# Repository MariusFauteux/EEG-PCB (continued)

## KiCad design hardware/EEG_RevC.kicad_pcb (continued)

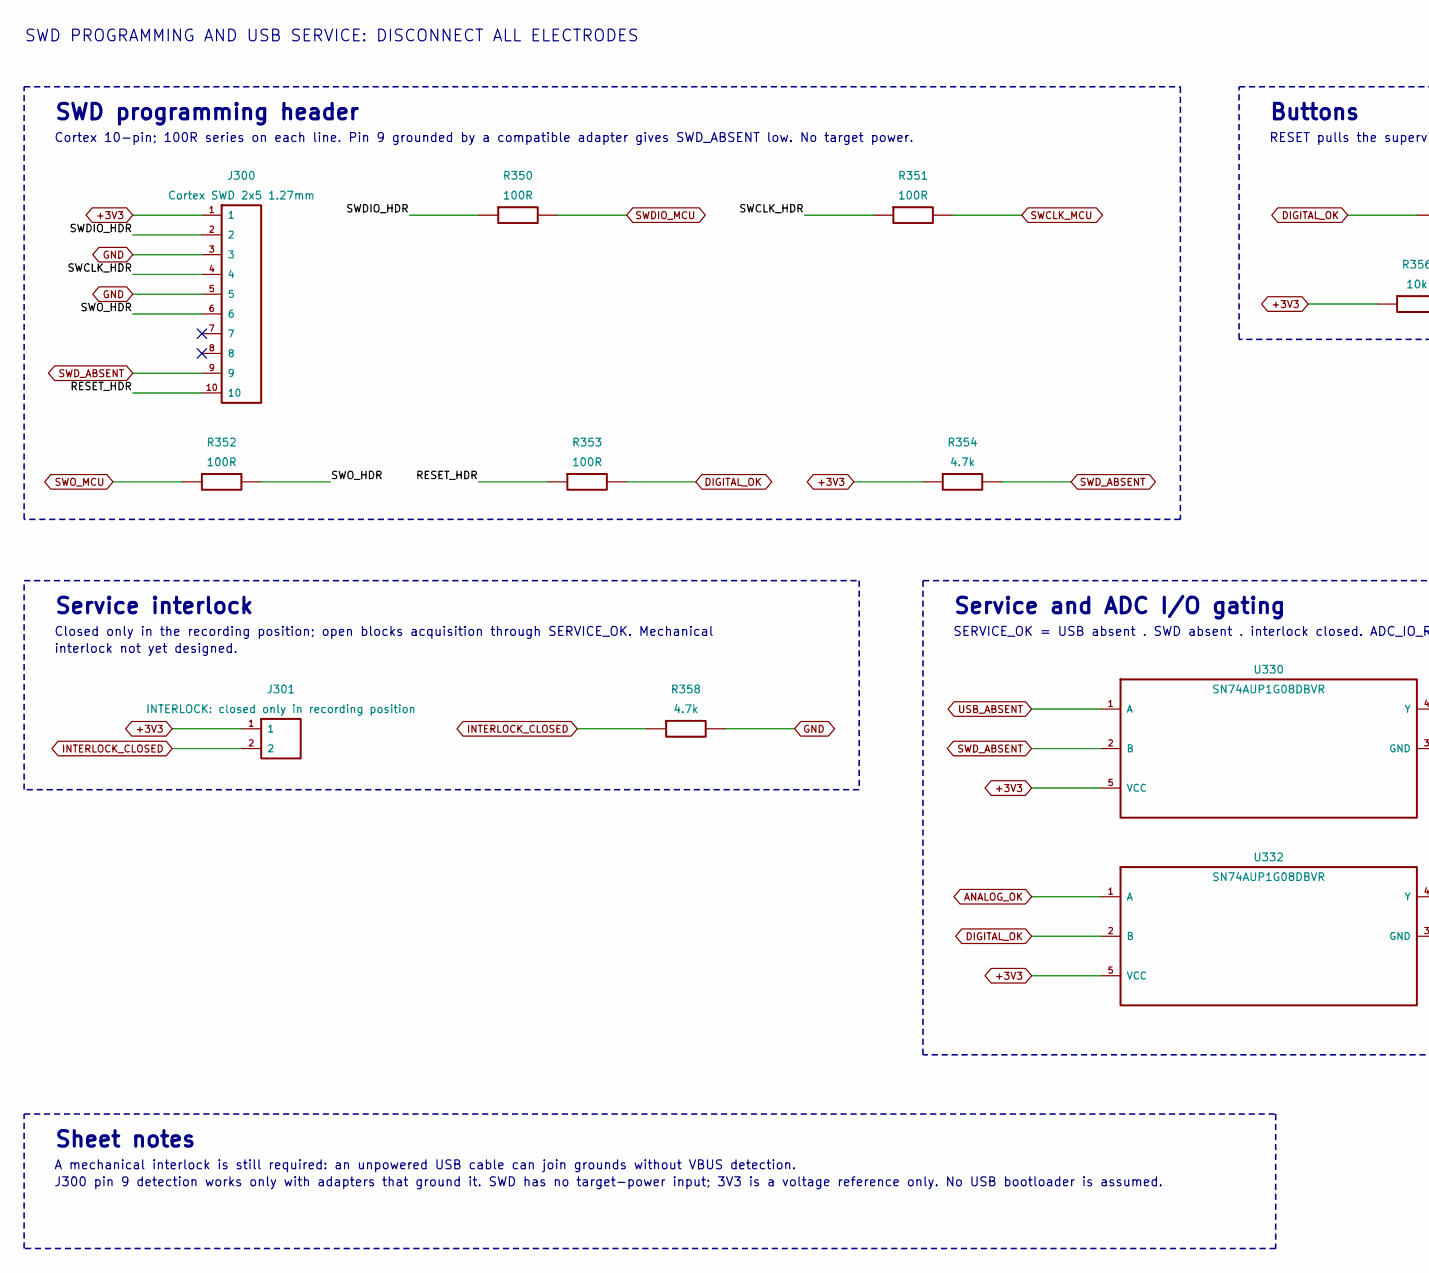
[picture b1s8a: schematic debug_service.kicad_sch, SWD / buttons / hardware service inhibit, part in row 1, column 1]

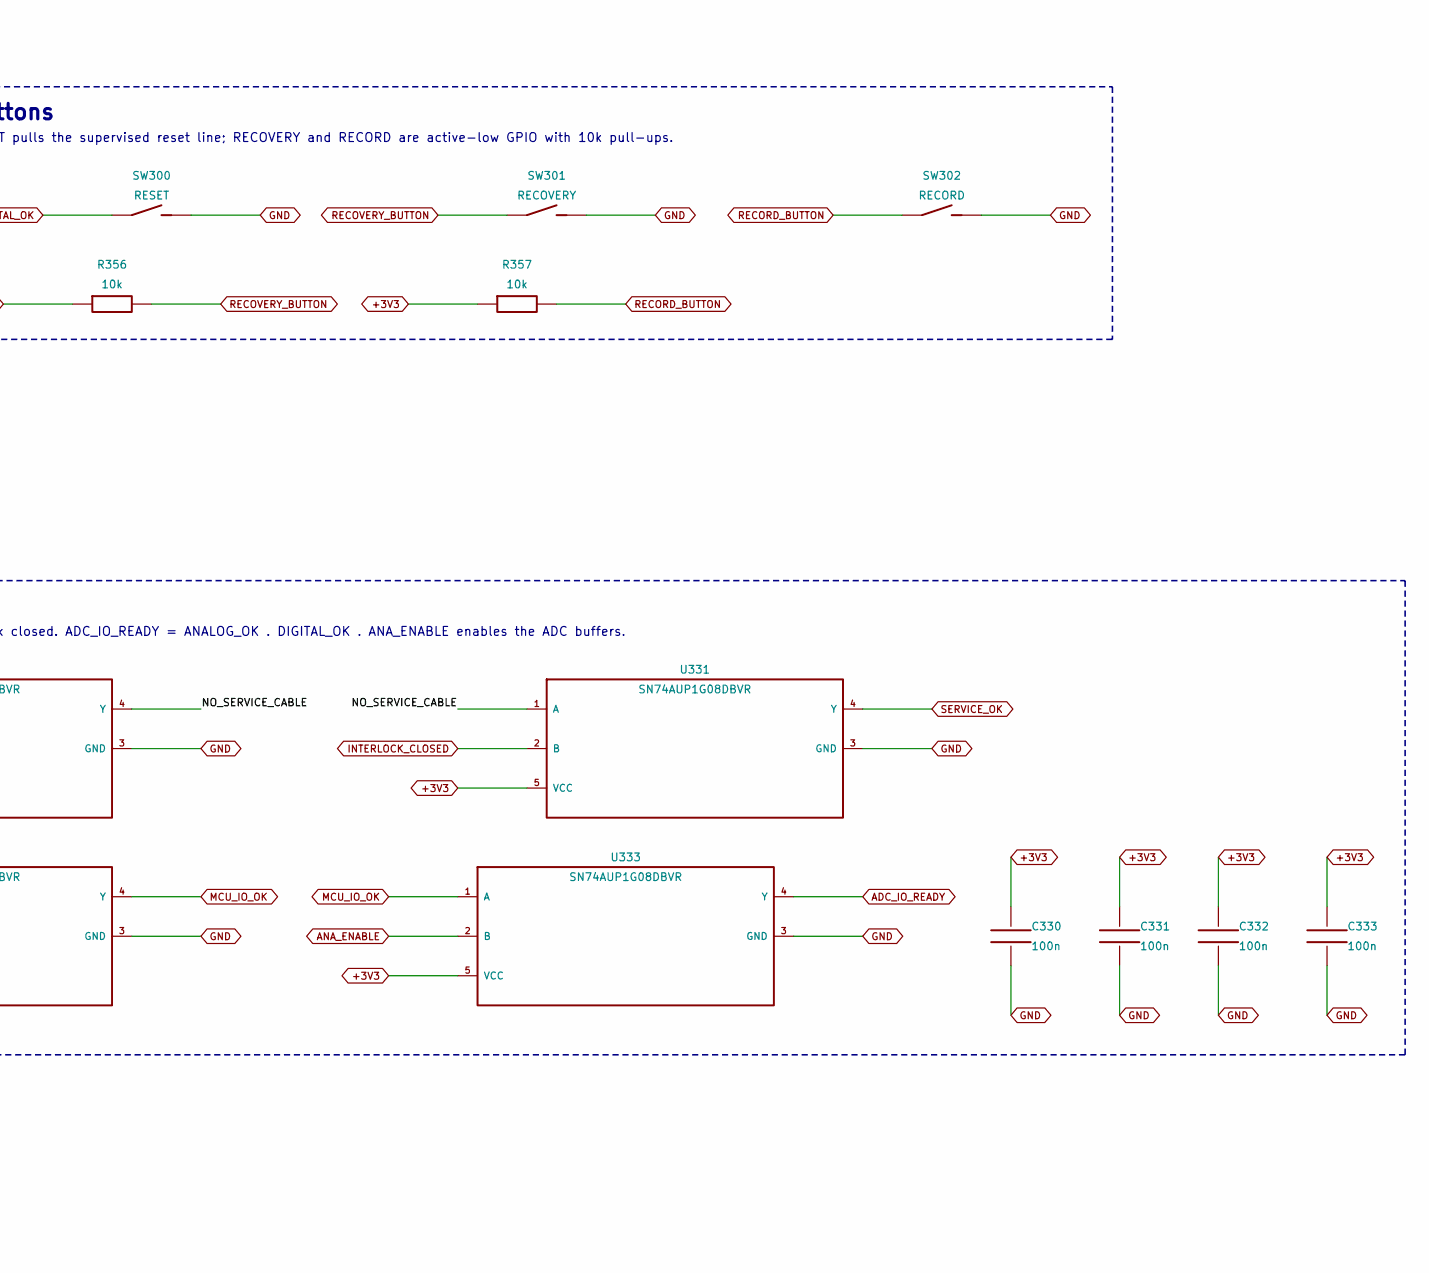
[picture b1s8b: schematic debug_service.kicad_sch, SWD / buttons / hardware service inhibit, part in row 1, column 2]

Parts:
C330, C331, C332, C333: 100n; C_0603_1608Metric; MPN GCM188R71H104KA57D
J300: Cortex SWD 2x5 1.27mm; PinHeader_2x05_P1.27mm_Vertical_SMD; MPN 3220-10-0300-00
J301: INTERLOCK: closed only in recording position; JST_PH_S2B-PH-K_1x02_P2.00mm_Horizontal; MPN S2B-PH-K-S
R350, R351, R352, R353: 100R; R_0603_1608Metric; MPN ERJ-3EKF1000V
R354, R358: 4.7k; R_0603_1608Metric; MPN ERJ-3EKF4701V
R356, R357: 10k; R_0603_1608Metric; MPN ERJ-3EKF1002V
SW300: RESET; SW_SPST_TL3342; MPN TL3342F160QG
SW301: RECOVERY; SW_SPST_TL3342; MPN TL3342F160QG
SW302: RECORD; SW_SPST_TL3342; MPN TL3342F160QG
U330, U331, U332, U333: SN74AUP1G08DBVR; SOT-23-5; MPN SN74AUP1G08DBVR

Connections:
+3V3: C330.1, C331.1, C332.1, C333.1, J300.1, J301.1, R354.1, R356.1, R357.1, U330.5 (VCC), U331.5 (VCC), U332.5 (VCC), U333.5 (VCC); also elsewhere on the board
/SWD / buttons / hardware service inhibit/NO_SERVICE_CABLE: U330.4 (Y), U331.1 (A)
/SWD / buttons / hardware service inhibit/RESET_HDR: J300.10, R353.1
/SWD / buttons / hardware service inhibit/SWCLK_HDR: J300.4, R351.1
/SWD / buttons / hardware service inhibit/SWDIO_HDR: J300.2, R350.1
/SWD / buttons / hardware service inhibit/SWO_HDR: J300.6, R352.2
ADC_IO_READY: U333.4 (Y); also elsewhere on the board
ANALOG_OK: U332.1 (A); also elsewhere on the board
ANA_ENABLE: U333.2 (B); also elsewhere on the board
DIGITAL_OK: R353.2, SW300.1, U332.2 (B); also elsewhere on the board
GND: C330.2, C331.2, C332.2, C333.2, J300.3, J300.5, R358.2, SW300.2, SW301.2, SW302.2, U330.3 (GND), U331.3 (GND), U332.3 (GND), U333.3 (GND); also elsewhere on the board
INTERLOCK_CLOSED: J301.2, R358.1, U331.2 (B); also elsewhere on the board
MCU_IO_OK: U332.4 (Y), U333.1 (A)
RECORD_BUTTON: R357.2, SW302.1; also elsewhere on the board
RECOVERY_BUTTON: R356.2, SW301.1; also elsewhere on the board
SERVICE_OK: U331.4 (Y); also elsewhere on the board
SWCLK_MCU: R351.2; also elsewhere on the board
SWDIO_MCU: R350.2; also elsewhere on the board
SWD_ABSENT: J300.9, R354.2, U330.2 (B)
SWO_MCU: R352.1; also elsewhere on the board
USB_ABSENT: U330.1 (A); also elsewhere on the board

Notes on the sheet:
SWD PROGRAMMING AND USB SERVICE: DISCONNECT ALL ELECTRODES
SWD programming header
Cortex 10-pin; 100R series on each line. Pin 9 grounded by a compatible adapter gives SWD_ABSENT low. No target power.
Buttons
RESET pulls the supervised reset line; RECOVERY and RECORD are active-low GPIO with 10k pull-ups.
Service interlock
Closed only in the recording position; open blocks acquisition through SERVICE_OK. Mechanical
interlock not yet designed.
Service and ADC I/O gating
SERVICE_OK = USB absent . SWD absent . interlock closed. ADC_IO_READY = ANALOG_OK . DIGITAL_OK . ANA_ENABLE enables the ADC buffers.
Sheet notes
A mechanical interlock is still required: an unpowered USB cable can join grounds without VBUS detection.
J300 pin 9 detection works only with adapters that ground it. SWD has no target-power input; 3V3 is a voltage reference only. No USB bootloader is assumed.

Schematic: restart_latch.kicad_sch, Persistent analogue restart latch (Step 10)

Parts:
C226, C227, C228: 100n; C_0603_1608Metric; MPN GCM188R71H104KA57D
TP230: RUN_ARMED; TestPoint_Pad_D1.0mm
U226, U228: SN74AUP1G08DBVR; SOT-23-5; MPN SN74AUP1G08DBVR
U227: SN74LVC1G74DCUR; VSSOP-8_2.3x2mm_P0.5mm; MPN SN74LVC1G74DCUR

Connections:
+3V3: C226.1, C227.1, C228.1, U226.5 (VCC), U227.2 (D), U227.7 (~PRE), U227.8 (VCC), U228.5 (VCC); also elsewhere on the board
GND: C226.2, C227.2, C228.2, U226.3 (GND), U227.4 (GND), U228.3 (GND); also elsewhere on the board
POWER_OK: U226.1 (A); also elsewhere on the board
RUN_ARMED: TP230.1, U227.5 (Q), U228.2 (B)
RUN_LATCHED: U228.4 (Y); also elsewhere on the board
RUN_PERMIT: U226.4 (Y), U227.6 (~CLR)
RUN_REQUEST: U227.1 (CLK), U228.1 (A); also elsewhere on the board
SERVICE_OK: U226.2 (B); also elsewhere on the board

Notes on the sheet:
PERSISTENT ANALOGUE RESTART LATCH (Step 10)
Run permit
RUN_PERMIT = POWER_OK . SERVICE_OK. Low on any SYS, pack or service fault.
Restart flip-flop
RUN_PERMIT low clears RUN_ARMED and holds it clear. A new RUN_REQUEST rising edge re-arms only while permitted. TP230 for
bench checks.
Latched run output
RUN_LATCHED = RUN_REQUEST . RUN_ARMED; replaces RUN_REQUEST in the analogue enable chain.
Sheet notes
ANA_ENABLE = SYS_OK . PACK_OK . SERVICE_OK . RUN_REQUEST . RUN_ARMED. Battery rebound cannot restart analogue power.
Power-up: supervisors hold POWER_OK low through their release delay, so U227 starts cleared.
Firmware: on any stop drive RUN_REQUEST low; to start, confirm SYS_OK and PACK_OK, hold RUN_REQUEST low >= 1 us, then high. Drive it directly from the GPIO (clock edge <= 10 ns/V, no RC).

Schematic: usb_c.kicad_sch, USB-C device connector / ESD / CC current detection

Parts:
C320, C322, C323: 100n; C_0603_1608Metric; MPN GCM188R71H104KA57D
C321: 1u 10V X7R; C_0805_2012Metric; MPN GCM21BR71E105KA56L
C324: 1u 50V X7R 0805 (VBUS_CON, at U323); C_0805_2012Metric; MPN GCM21BR71H105KA03L
C325: 1u 25V X7R 0805 (VBUS_POWER LDO); C_0805_2012Metric; MPN GCM21BR71E105KA56L
C326: 1u 25V X7R 0805 (LDO IN); C_0805_2012Metric; MPN GCM21BR71E105KA56L
C327: 1u 25V X7R 0805 (LDO OUT, module VBUS); C_0805_2012Metric; MPN GCM21BR71E105KA56L
D310, D311, D312: TPD2E2U06DCKR; SOT-323_SC-70; MPN TPD2E2U06DCKR
D324: BAT54 (U324 reverse-current bypass); SOT-23; MPN BAT54,215
J310: USB4105-GF-A; USB_C_Receptacle_GCT_USB4105-xx-A_16P_TopMnt_Horizontal; MPN USB4105-GF-A
R360: 887k 1%; R_0603_1608Metric; MPN ERJ-3EKF8873V
R361: 10k; R_0603_1608Metric; MPN ERJ-3EKF1002V
R362: 10k 1%; R_0603_1608Metric; MPN ERJ-3EKF1002V
R363: 100k 1%; R_0603_1608Metric; MPN ERJ-3EKF1003V
U320: TUSB320LAIRWBR; Texas_RWB0012A_X2QFN-12_1.6x1.6mm_P0.4mm; MPN TUSB320LAIRWBR
U321, U322: SN74LVC1G14DBVR; SOT-23-5; MPN SN74LVC1G14DBVR
U323: TPD1S514-1YZR (VBUS OVP 5.9-5.99 V); Texas_YZ0012_DSBGA-12_P0.4mm; MPN TPD1S514-1YZR
U324: TPS7A2050PDBVR (module VBUS 5.0 V); SOT-23-5; MPN TPS7A2050PDBVR

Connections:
+3V3: C320.1, C322.1, C323.1, R361.1, U320.12 (VDD), U321.5 (VCC), U322.5 (VCC); also elsewhere on the board
/USB-C device connector / ESD / CC current detection/USB_SENSE_LOGIC: R362.2, R363.1, U321.2 (A)
/USB-C device connector / ESD / CC current detection/VBUS_DETECT_R: R360.2, U320.4 (VBUS_DET)
CC1: D311.1 (IO1), J310.A5 (CC1), U320.1 (CC1)
CC2: D311.2 (IO2), J310.B5 (CC2), U320.2 (CC2)
GND: C320.2, C321.2, C322.2, C323.2, C324.2, C325.2, C326.2, C327.2, D310.3 (GND), D311.3 (GND), D312.3 (GND), J310.A1 (GND), J310.A12 (GND), J310.B1 (GND), J310.B12 (GND), J310.SH (SHIELD), R363.2, U320.3 (PORT), U320.5 (ADDR), U320.10 (GND), U320.11 (EN_N), U321.3 (GND), U322.3 (GND), U323.A1 (~EN), U323.A4 (GND), U323.B4 (GND), U323.C1 (GND), U323.C4 (GND), U324.2 (GND); also elsewhere on the board
MCU_VBUS: C327.1, D324.1 (A), U324.5 (OUT); also elsewhere on the board
POWER_SCL: U320.8 (SCL); also elsewhere on the board
POWER_SDA: U320.7 (SDA); also elsewhere on the board
USB_5V: C321.1, C326.1, D312.1 (IO1), D312.2 (IO2), D324.3 (K), U323.A2 (VBUS_SYS), U323.A3 (VBUS_SYS), U323.B2 (VBUS_SYS), U324.1 (IN), U324.3 (EN); also elsewhere on the board
USB_ABSENT: U321.4 (Y), U322.2 (A); also elsewhere on the board
USB_CC_INT_N: R361.2, U320.6 (INT_N); also elsewhere on the board
USB_DM: D310.2 (IO2), J310.A7 (D-), J310.B7 (D-); also elsewhere on the board
USB_DP: D310.1 (IO1), J310.A6 (D+), J310.B6 (D+); also elsewhere on the board
USB_PRESENT: U322.4 (Y); also elsewhere on the board
USB_VPWR: C325.1, R362.1, U323.B1 (VBUS_POWER)
VBUS_CON: C324.1, J310.A4 (VBUS), J310.A9 (VBUS), J310.B4 (VBUS), J310.B9 (VBUS), R360.1, U323.B3 (VBUS_CON), U323.C2 (VBUS_CON), U323.C3 (VBUS_CON)

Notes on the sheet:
USB-C 5 V SINK - NO PD, DATA TO MODULE, VBUS OVERVOLTAGE CUT-OFF, VBUS TO THE BQ25798 CHARGER
USB-C receptacle and ESD
USB 2.0 data to the module; duplicate contacts joined. TPD2E2U06 on D+/D-, CC and USB_5V is ESD only. J310 VBUS contacts are VBUS_CON, before the overvoltage switch.
VBUS overvoltage switch (Step 14)
TPD1S514-1: OVP 5.90-5.99 V, off in 100 ns, 30 V DC and 100 V surge on VBUS_CON, 39 mOhm. 20 ms delay + 3.5 ms soft start at plug-in, so the source sees
only C324 at attach. EN low: always enabled. VBUS_POWER (USB_VPWR, <= 5.5 V) feeds the USB-sense divider.
Module VBUS regulator (Step 14)
TPS7A2050: 5.0 V +/-1.5 % to module pad 31, because the nRF52840 VBUS pin is rated 5.5 V (5.8 V absolute) and the OVP ceiling is 5.99 V. D324 BAT54
carries reverse current to USB_5V after unplug (TI: <= 15 mA through the LDO).
CC sink controller
TUSB320LAI presents sink terminations and reports advertised current over I2C. No PD. VBUS_DET through 887k from the connector side (TI: system VBUS up to 28 V).
VBUS presence logic
Divider from USB_VPWR and Schmitt inverters give USB_ABSENT (gates SERVICE_OK) and USB_PRESENT (to MCU), also while U323 blocks an overvoltage source.
Sheet notes
Step 14: U323 TPD1S514-1 disconnects USB_5V from the connector above 5.99 V within 100 ns; VBUS_CON is rated 30 V DC. No duplicate Rd: the CC controller contains the sink terminations.
Route the USB 2.0 pair short and matched, directly to the module. Place U323 and C324 next to J310; keep VBUS_CON copper short and on the top layer (TI layout guide).

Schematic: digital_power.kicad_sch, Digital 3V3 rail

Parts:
C240: 10u 25V X7R 1206 (SYS); C_1206_3216Metric; MPN GRM31CR71E106KA12L
C241: 22u 25V X7R 1210; C_1210_3225Metric; MPN GRM32ER71E226KE15L
C242: 100n; C_0603_1608Metric; MPN GCM188R71H104KA57D
L240: 2.2uH XFL4020-222MEC; L_Coilcraft_XxL4020; MPN XFL4020-222MEC
R240: 100k; R_0603_1608Metric; MPN ERJ-3EKF1003V
R380, R382, R383: 100k reserved default; R_0603_1608Metric; MPN ERJ-3EKF1003V
U240: TPS62162DSGR; Texas_DSG0008A_WSON-8-1EP_2x2mm_P0.5mm_EP0.9x1.6mm; MPN TPS62162DSGR

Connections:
+3V3: C241.1, C242.1, L240.2, R240.1, U240.6 (VOS); also elsewhere on the board
/Digital 3V3 rail/BUCK_PG: R240.2, U240.8 (PG)
/Digital 3V3 rail/SW_DIG: L240.1, U240.7 (SW)
CHARGE_REQUEST: R380.1; also elsewhere on the board
GND: C240.2, C241.2, C242.2, R380.2, R382.2, R383.2, U240.1 (PGND), U240.4 (AGND), U240.5 (FB), U240.9 (EP); also elsewhere on the board
SD_POWER_EN: R383.1; also elsewhere on the board
STATUS_LED: R382.1; also elsewhere on the board
SYS: C240.1, U240.2 (VIN), U240.3 (EN); also elsewhere on the board

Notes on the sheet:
DIGITAL 3.3 V RAIL FROM SYS
3.3 V buck regulator
TPS62162 from SYS. Supplies module, logic, microSD and ADC DVDD. BUCK_PG is informational; DIGITAL_OK supervises.
Reserved control defaults
Pull-downs keep reserved MCU outputs (charge request, power hold, LED, SD power) defined until those circuits exist.
Sheet notes
TPS62162 runs whenever SYS is up: from the pack, or from USB through the charger. Soft-off is the BQ25798 ship mode (charger sheet), which removes SYS entirely.

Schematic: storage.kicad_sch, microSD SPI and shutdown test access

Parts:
C420: 22u 25V X7R 1210; C_1210_3225Metric; MPN GRM32ER71E226KE15L
C421: 100n 10V X7R; C_0603_1608Metric; MPN GCM188R71H104KA57D
C422: 10n; C_0603_1608Metric; MPN GCM1885C1H103JA16D
D420, D421, D422, D423: TPD2E2U06DCKR; SOT-323_SC-70; MPN TPD2E2U06DCKR
J420: DM3AT-SF-PEJM5; microSD_HC_Hirose_DM3AT-SF-PEJM5; MPN DM3AT-SF-PEJM5
R420, R421, R422, R423: 33R; R_0603_1608Metric; MPN ERJ-3EKF33R0V
R424, R425, R426, R427, R428, R430: 10k 1%; R_0603_1608Metric; MPN ERJ-3EKF1002V
R429: 100k; R_0603_1608Metric; MPN ERJ-3EKF1003V
R431: 100R; R_0603_1608Metric; MPN ERJ-3EKF1000V
TP420: +3V3; TestPoint_Pad_D1.0mm
TP421: GND; TestPoint_Pad_D1.0mm
TP422: BAT_WARN_OK; TestPoint_Pad_D1.0mm
TP423: SYS_OK; TestPoint_Pad_D1.0mm
TP424: PACK_OK; TestPoint_Pad_D1.0mm
TP425: DIGITAL_OK; TestPoint_Pad_D1.0mm

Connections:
+3V3: C420.1, C421.1, D423.2 (IO2), J420.4 (VDD), R424.1, R425.1, R426.1, R427.1, R428.1, R430.1, TP420.1; also elsewhere on the board
/microSD SPI and shutdown test access/CARD_CLK: D420.1 (IO1), J420.5 (CLK), R420.2
/microSD SPI and shutdown test access/CARD_CS_N: D421.1 (IO1), J420.2 (DAT3_CS_N), R422.2, R425.2
/microSD SPI and shutdown test access/CARD_DAT1: D422.1 (IO1), J420.8 (DAT1), R427.2
/microSD SPI and shutdown test access/CARD_DAT2: D422.2 (IO2), J420.1 (DAT2), R428.2
/microSD SPI and shutdown test access/CARD_DETECT_RAW_N: D423.1 (IO1), J420.9 (CD_B), R430.2, R431.1
/microSD SPI and shutdown test access/CARD_DI: D420.2 (IO2), J420.3 (CMD_DI), R421.2, R424.2
/microSD SPI and shutdown test access/CARD_DO: D421.2 (IO2), J420.7 (DAT0_DO), R423.2, R426.2
BAT_WARN_OK: TP422.1; also elsewhere on the board
DIGITAL_OK: TP425.1; also elsewhere on the board
GND: C420.2, C421.2, C422.2, D420.3 (GND), D421.3 (GND), D422.3 (GND), D423.3 (GND), J420.6 (VSS), J420.10 (CD_A), J420.SH (SHELL_x4), R429.2, TP421.1; also elsewhere on the board
PACK_OK: TP424.1; also elsewhere on the board
SD_CS_N: R422.1; also elsewhere on the board
SD_DETECT_N: C422.1, R431.2; also elsewhere on the board
SD_MISO: R423.1; also elsewhere on the board
SD_MOSI: R421.1; also elsewhere on the board
SD_SCLK: R420.1, R429.1; also elsewhere on the board
SYS_OK: TP423.1; also elsewhere on the board

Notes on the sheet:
microSD STORAGE (SPI, 3V3) - REMOVE CARD ONLY WITH BOARD POWER OFF
microSD socket and supply
DM3AT socket on the shared 3V3 rail; 22 uF bulk plus 100 nF. Remove the card only with power off.
SPI series resistors
33R damping between module and card; 100k keeps SCLK low at reset.
Card line pull-ups
10k on CMD/DAT lines as required by the SD SPI-mode start-up.
Card detect
Switch to GND, 10k pull-up and 100R/10 nF filter to SD_DETECT_N; software debounce.
Card-side ESD
TPD2E2U06 pairs at the socket on every card line and card detect.
Supply and status test points
Bench access to rails and supervisor outputs for shutdown testing.
Sheet notes
No load switch or hold-up reservoir; SD_POWER_EN is reserved. All card pull-ups use the shared 3V3 rail.
BAT_WARN_OK low: stop capture, drain queue, wait for card ready, sync best effort. No guaranteed flush interval.

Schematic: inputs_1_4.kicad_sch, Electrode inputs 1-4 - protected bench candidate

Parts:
C1, C2, C3, C4: 220p C0G 5% 50V; C_0603_1608Metric; MPN GCM1885C1H221JA16D
D501, D502, D503, D504: TPD2E2U06DCKR; SOT-323_SC-70; MPN TPD2E2U06DCKR
J1: CH1+
J2: CH1-
J3: CH2+
J4: CH2-
J5: CH3+
J6: CH3-
J7: CH4+
J8: CH4-
JP1, JP2, JP3, JP4: 1-2 bipolar / 2-3 REF; PinHeader_1x03_P2.54mm_Vertical; MPN 61300311121
R11, R12, R13, R14, R21, R22, R23, R24, R31, R32, R33, R34, R41, R42, R43, R44: 47k 0.1%; R_0805_2012Metric; MPN ERJ-PB6B4702V
R501, R502, R503, R504, R505, R506, R507, R508: 4.7k 0.1%; R_0805_2012Metric; MPN ERJ-PB6B4701V

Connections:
/Electrode inputs 1-4 - protected bench candidate/CLAMP1N: D501.2 (IO2), R14.2, R502.1
/Electrode inputs 1-4 - protected bench candidate/CLAMP1P: D501.1 (IO1), R12.2, R501.1
/Electrode inputs 1-4 - protected bench candidate/CLAMP2N: D502.2 (IO2), R24.2, R504.1
/Electrode inputs 1-4 - protected bench candidate/CLAMP2P: D502.1 (IO1), R22.2, R503.1
/Electrode inputs 1-4 - protected bench candidate/CLAMP3N: D503.2 (IO2), R34.2, R506.1
/Electrode inputs 1-4 - protected bench candidate/CLAMP3P: D503.1 (IO1), R32.2, R505.1
/Electrode inputs 1-4 - protected bench candidate/CLAMP4N: D504.2 (IO2), R44.2, R508.1
/Electrode inputs 1-4 - protected bench candidate/CLAMP4P: D504.1 (IO1), R42.2, R507.1
/Electrode inputs 1-4 - protected bench candidate/NSEL1: JP1.2, R13.1
/Electrode inputs 1-4 - protected bench candidate/NSEL2: JP2.2, R23.1
/Electrode inputs 1-4 - protected bench candidate/NSEL3: JP3.2, R33.1
/Electrode inputs 1-4 - protected bench candidate/NSEL4: JP4.2, R43.1
ADC_IN1N: C1.2, R502.2; also elsewhere on the board
ADC_IN1P: C1.1, R501.2; also elsewhere on the board
ADC_IN2N: C2.2, R504.2; also elsewhere on the board
ADC_IN2P: C2.1, R503.2; also elsewhere on the board
ADC_IN3N: C3.2, R506.2; also elsewhere on the board
ADC_IN3P: C3.1, R505.2; also elsewhere on the board
ADC_IN4N: C4.2, R508.2; also elsewhere on the board
ADC_IN4P: C4.1, R507.2; also elsewhere on the board
E1N: J2.1, JP1.1; also elsewhere on the board
E1P: J1.1, R11.1; also elsewhere on the board
E2N: J4.1, JP2.1; also elsewhere on the board
E2P: J3.1, R21.1; also elsewhere on the board
E3N: J6.1, JP3.1; also elsewhere on the board
E3P: J5.1, R31.1; also elsewhere on the board
E4N: J8.1, JP4.1; also elsewhere on the board
E4P: J7.1, R41.1; also elsewhere on the board
GND: D501.3 (GND), D502.3 (GND), D503.3 (GND), D504.3 (GND); also elsewhere on the board
unnamed: R11.2, R12.1
unnamed: R13.2, R14.1
unnamed: R21.2, R22.1
unnamed: R23.2, R24.1
unnamed: R31.2, R32.1
unnamed: R33.2, R34.1
unnamed: R41.2, R42.1
unnamed: R43.2, R44.1
REF_BUF: JP1.3, JP2.3, JP3.3, JP4.3; also elsewhere on the board

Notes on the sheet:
ELECTRODE INPUTS CH1-CH4 - 94k BEFORE CLAMP, 4.7k AFTER CLAMP. NO HUMAN CONNECTION
Channel 1 input network
CH1+ and CH1- each pass 2 x 47k, the TVS clamp, then 4.7k into the ADC; 220 pF C0G across the pair. JP1 selects bipolar (1-2) or the buffered shared REF, REF_BUF (2-3), for the negative leg.
Channel 2 input network
CH2+ and CH2- each pass 2 x 47k, the TVS clamp, then 4.7k into the ADC; 220 pF C0G across the pair. JP2 selects bipolar (1-2) or the buffered shared REF, REF_BUF (2-3), for the negative leg.
Channel 3 input network
CH3+ and CH3- each pass 2 x 47k, the TVS clamp, then 4.7k into the ADC; 220 pF C0G across the pair. JP3 selects bipolar (1-2) or the buffered shared REF, REF_BUF (2-3), for the negative leg.
Channel 4 input network
CH4+ and CH4- each pass 2 x 47k, the TVS clamp, then 4.7k into the ADC; 220 pF C0G across the pair. JP4 selects bipolar (1-2) or the buffered shared REF, REF_BUF (2-3), for the negative leg.
Sheet notes
TPD2E2U06 leakage limit applies at 2.5 V. The ground clamp is not isolation. Fit one shunt per JP; change it with power off.
JP pin 3 is REF_BUF, the buffered REF electrode; it passes through the same negative-leg network as a bipolar electrode. No extra capacitors from inputs to GND.

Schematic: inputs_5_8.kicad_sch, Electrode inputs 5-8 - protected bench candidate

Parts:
C5, C6, C7, C8: 220p C0G 5% 50V; C_0603_1608Metric; MPN GCM1885C1H221JA16D
D505, D506, D507, D508: TPD2E2U06DCKR; SOT-323_SC-70; MPN TPD2E2U06DCKR
J9: CH5+
J10: CH5-
J11: CH6+
J12: CH6-
J13: CH7+
J14: CH7-
J15: CH8+
J16: CH8-
JP5, JP6, JP7, JP8: 1-2 bipolar / 2-3 REF; PinHeader_1x03_P2.54mm_Vertical; MPN 61300311121
R51, R52, R53, R54, R61, R62, R63, R64, R71, R72, R73, R74, R81, R82, R83, R84: 47k 0.1%; R_0805_2012Metric; MPN ERJ-PB6B4702V
R509, R510, R511, R512, R513, R514, R515, R516: 4.7k 0.1%; R_0805_2012Metric; MPN ERJ-PB6B4701V

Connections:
/Electrode inputs 5-8 - protected bench candidate/CLAMP5N: D505.2 (IO2), R54.2, R510.1
/Electrode inputs 5-8 - protected bench candidate/CLAMP5P: D505.1 (IO1), R52.2, R509.1
/Electrode inputs 5-8 - protected bench candidate/CLAMP6N: D506.2 (IO2), R64.2, R512.1
/Electrode inputs 5-8 - protected bench candidate/CLAMP6P: D506.1 (IO1), R62.2, R511.1
/Electrode inputs 5-8 - protected bench candidate/CLAMP7N: D507.2 (IO2), R74.2, R514.1
/Electrode inputs 5-8 - protected bench candidate/CLAMP7P: D507.1 (IO1), R72.2, R513.1
/Electrode inputs 5-8 - protected bench candidate/CLAMP8N: D508.2 (IO2), R84.2, R516.1
/Electrode inputs 5-8 - protected bench candidate/CLAMP8P: D508.1 (IO1), R82.2, R515.1
/Electrode inputs 5-8 - protected bench candidate/NSEL5: JP5.2, R53.1
/Electrode inputs 5-8 - protected bench candidate/NSEL6: JP6.2, R63.1
/Electrode inputs 5-8 - protected bench candidate/NSEL7: JP7.2, R73.1
/Electrode inputs 5-8 - protected bench candidate/NSEL8: JP8.2, R83.1
ADC_IN5N: C5.2, R510.2; also elsewhere on the board
ADC_IN5P: C5.1, R509.2; also elsewhere on the board
ADC_IN6N: C6.2, R512.2; also elsewhere on the board
ADC_IN6P: C6.1, R511.2; also elsewhere on the board
ADC_IN7N: C7.2, R514.2; also elsewhere on the board
ADC_IN7P: C7.1, R513.2; also elsewhere on the board
ADC_IN8N: C8.2, R516.2; also elsewhere on the board
ADC_IN8P: C8.1, R515.2; also elsewhere on the board
E5N: J10.1, JP5.1; also elsewhere on the board
E5P: J9.1, R51.1; also elsewhere on the board
E6N: J12.1, JP6.1; also elsewhere on the board
E6P: J11.1, R61.1; also elsewhere on the board
E7N: J14.1, JP7.1; also elsewhere on the board
E7P: J13.1, R71.1; also elsewhere on the board
E8N: J16.1, JP8.1; also elsewhere on the board
E8P: J15.1, R81.1; also elsewhere on the board
GND: D505.3 (GND), D506.3 (GND), D507.3 (GND), D508.3 (GND); also elsewhere on the board
unnamed: R51.2, R52.1
unnamed: R53.2, R54.1
unnamed: R61.2, R62.1
unnamed: R63.2, R64.1
unnamed: R71.2, R72.1
unnamed: R73.2, R74.1
unnamed: R81.2, R82.1
unnamed: R83.2, R84.1
REF_BUF: JP5.3, JP6.3, JP7.3, JP8.3; also elsewhere on the board

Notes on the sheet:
ELECTRODE INPUTS CH5-CH8 - 94k BEFORE CLAMP, 4.7k AFTER CLAMP. NO HUMAN CONNECTION
Channel 5 input network
CH5+ and CH5- each pass 2 x 47k, the TVS clamp, then 4.7k into the ADC; 220 pF C0G across the pair. JP5 selects bipolar (1-2) or the buffered shared REF, REF_BUF (2-3), for the negative leg.
Channel 6 input network
CH6+ and CH6- each pass 2 x 47k, the TVS clamp, then 4.7k into the ADC; 220 pF C0G across the pair. JP6 selects bipolar (1-2) or the buffered shared REF, REF_BUF (2-3), for the negative leg.
Channel 7 input network
CH7+ and CH7- each pass 2 x 47k, the TVS clamp, then 4.7k into the ADC; 220 pF C0G across the pair. JP7 selects bipolar (1-2) or the buffered shared REF, REF_BUF (2-3), for the negative leg.
Channel 8 input network
CH8+ and CH8- each pass 2 x 47k, the TVS clamp, then 4.7k into the ADC; 220 pF C0G across the pair. JP8 selects bipolar (1-2) or the buffered shared REF, REF_BUF (2-3), for the negative leg.
Sheet notes
TPD2E2U06 leakage limit applies at 2.5 V. The ground clamp is not isolation. Fit one shunt per JP; change it with power off.
JP pin 3 is REF_BUF, the buffered REF electrode; it passes through the same negative-leg network as a bipolar electrode. No extra capacitors from inputs to GND.

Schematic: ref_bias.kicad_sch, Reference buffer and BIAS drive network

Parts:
C500: 100n 16V X7R (at U500 V+); C_0603_1608Metric; MPN GCM188R71H104KA57D
C501: 1u 10V X7R; C_0805_2012Metric; MPN GCM21BR71E105KA56L
CFB1: 10n C0G 5% 50V; C_0603_1608Metric; MPN GCM1885C1H103JA16D
D509, D510: TPD2E2U06DCKR; SOT-323_SC-70; MPN TPD2E2U06DCKR
J500: ELECTRODE HARNESS 2x10 (keyed box header); IDC-Header_2x10_P2.54mm_Vertical; MPN 61202021621
JBIAS1: BIAS electrode
JP9: REF test: REF electrode -> CH8- (JP8 1-2); PinHeader_1x02_P2.54mm_Vertical; MPN 61300211121
JP10: BIAS test: BIAS electrode -> CH7- (JP7 1-2); PinHeader_1x02_P2.54mm_Vertical; MPN 61300211121
JREF1: REF electrode
R517, R518: 47k 0.1%; R_0805_2012Metric; MPN ERJ-PB6B4702V
R519: 4.7k 0.1%; R_0805_2012Metric; MPN ERJ-PB6B4701V
RB1, RB2: 499k 0.1%; R_0805_2012Metric; MPN ERJ-PB6B4993V
RFB1: 1M; R_0805_2012Metric; MPN ERJ-PB6B1004V
RZB1: 100k 0.1%; R_0805_2012Metric; MPN ERJ-PB6B1003V
U500: OPA376AIDBVR; SOT-23-5; MPN OPA376AIDBVR

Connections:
+5VA: C500.1, C501.1, U500.5 (V+); also elsewhere on the board
/Reference buffer and BIAS drive network/BIAS_COMP: CFB1.2, RZB1.1
/Reference buffer and BIAS drive network/BIAS_MID: D509.1 (IO1), D509.2 (IO2), RB1.2, RB2.1
/Reference buffer and BIAS drive network/REF_BUF_IN: R519.2, U500.3 (+IN)
/Reference buffer and BIAS drive network/REF_CLAMP: D510.1 (IO1), D510.2 (IO2), R518.2, R519.1
/Reference buffer and BIAS drive network/REF_MID: R517.2, R518.1
ADC_BIASINV: RFB1.2, RZB1.2; also elsewhere on the board
ADC_BIASOUT: CFB1.1, RB1.1, RFB1.1; also elsewhere on the board
BIAS_ELEC: J500.18, JBIAS1.1, JP10.1, RB2.2
E1N: J500.2; also elsewhere on the board
E1P: J500.1; also elsewhere on the board
E2N: J500.4; also elsewhere on the board
E2P: J500.3; also elsewhere on the board
E3N: J500.6; also elsewhere on the board
E3P: J500.5; also elsewhere on the board
E4N: J500.8; also elsewhere on the board
E4P: J500.7; also elsewhere on the board
E5N: J500.10; also elsewhere on the board
E5P: J500.9; also elsewhere on the board
E6N: J500.12; also elsewhere on the board
E6P: J500.11; also elsewhere on the board
E7N: J500.14, JP10.2; also elsewhere on the board
E7P: J500.13; also elsewhere on the board
E8N: J500.16, JP9.2; also elsewhere on the board
E8P: J500.15; also elsewhere on the board
GND: C500.2, C501.2, D509.3 (GND), D510.3 (GND), U500.2 (V-); also elsewhere on the board
REF_BUF: U500.1 (OUT), U500.4 (-IN); also elsewhere on the board
REF_RAW: J500.17, JP9.1, JREF1.1, R517.1

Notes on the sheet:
REFERENCE BUFFER AND BIAS ELECTRODES - STEP 12 BUFFERED REF, STEP 8 BIAS LOOP, BENCH ONLY
REF electrode and buffer (Step 12)
REF electrode -> 2 x 47k -> D510 clamp -> 4.7k -> OPA376 unity follower. REF_BUF feeds JP1-JP8 pin 3; each selected channel keeps its own 94k / clamp / 4.7k. U500 on +5VA, so it is off and clamped with the
ADC.
BIAS output network
RB1 + RB2 (2 x 499k) limit body current; D509 clamps the midpoint to GND.
Electrode harness J500 (Step 13)
J500 2x10 keyed box header: pins 1-16 CH1+ to CH8- (odd +, even -), 17 REF, 18 BIAS, 19-20 unused. The electrode symbols
J1-J16, JREF1 and JBIAS1 are the off-board leads.
Electrode impedance test links (Rev C12)
Normally open. JP9 puts the REF electrode on CH8- (set JP8 1-2, no CH8- electrode); JP10 puts the BIAS electrode on CH7- (set
JP7 1-2, no CH7- electrode). The ADS1299 lead-off source then measures it through the channel's own 94k network.
BIAS loop compensation
Lead-lag feedback 1M || (100k + 10 nF C0G) between BIASOUT and BIASINV for >= 47 deg modelled phase margin.
Sheet notes
REF is an electrode, not the ADC reference and not GND. It now drives only the U500 follower: channels on REF share no electrode impedance, and the REF electrode carries one leg of leakage instead of up
to eight.
Firmware: set BIASREF_INT = 1 in the same CONFIG3 write that sets PD_BIAS = 1; monitor BIAS_STAT.
Do not inject sustained overvoltage or connect a person. RB1/RB2 need pulse- and voltage-rated parts. +5VA backfeed is clamped by Q201 (analog sheet).

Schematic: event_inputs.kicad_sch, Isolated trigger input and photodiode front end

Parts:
C600: 100n 10V X7R (within 1 cm of U600 pins 4/6); C_0603_1608Metric; MPN GCM188R71H104KA57D
C610: 15p C0G 5% 50V 0402; C_0402_1005Metric; MPN GCM1555C1H150JA16D
C611, C614: 100n; C_0603_1608Metric; MPN GCM188R71H104KA57D
C612, C613, C615: 100n 10V X7R; C_0603_1608Metric; MPN GCM188R71H104KA57D
D600: 1N4148WS (LED reverse clamp); D_SOD-323; MPN 1N4148WS-7-F
D601: TPD2E2U06DCKR; SOT-323_SC-70; MPN TPD2E2U06DCKR
J600: TRIGGER IN (BNC, shell = isolated return); BNC_Amphenol_031-6575_Horizontal; MPN 031-6575
J601: PHOTODIODE (K, A; part TBD); JST_PH_S2B-PH-K_1x02_P2.00mm_Horizontal; MPN S2B-PH-K-S
R600: 620R 1% 0.25W; R_1206_3216Metric; MPN ERJ-8ENF6200V
R601, R616: 100R; R_0603_1608Metric; MPN ERJ-3EKF1000V
R610, R617: 1k; R_0603_1608Metric; MPN ERJ-3EKF1001V
R611: 33k 0.1%; R_0603_1608Metric; MPN ERA-3ARB333V
R612: 64.9k 1%; R_0603_1608Metric; MPN ERJ-3EKF6492V
R613: 1k 1%; R_0603_1608Metric; MPN ERJ-3EKF1001V
R614: 10k; R_0603_1608Metric; MPN ERJ-3EKF1002V
R615: 1M; R_0603_1608Metric; MPN ERJ-3EKF1004V
U600: TLP2761(TP,E); SO-6L_10x3.84mm_P1.27mm; MPN TLP2761(TP,E)
U610: TLV9061IDBVR; SOT-23-5; MPN TLV9061IDBVR
U611: TLV7011DCKR; SOT-353_SC-70-5; MPN TLV7011DCKR
U612: MCP4725A0T-E/CH (I2C 0x60); SOT-23-6; MPN MCP4725A0T-E/CH

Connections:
+3V3: C600.1, C612.1, C613.1, C615.1, R612.1, U600.6 (VCC), U610.5 (V+), U611.5 (VCC), U612.3 (VDD); also elsewhere on the board
/Isolated trigger input and photodiode front end/PHOTO_CMP: R615.1, R616.1, U611.1 (OUT)
/Isolated trigger input and photodiode front end/PHOTO_DAC: R617.1, U612.1 (VOUT)
/Isolated trigger input and photodiode front end/PHOTO_HYS: R614.2, R615.2, U611.3 (IN+)
/Isolated trigger input and photodiode front end/PHOTO_K_RAW: D601.1 (IO1), D601.2 (IO2), J601.1, R610.1
/Isolated trigger input and photodiode front end/PHOTO_REF: C611.1, R612.2, R613.1, U610.3 (IN+)
/Isolated trigger input and photodiode front end/PHOTO_SUM: C610.1, R610.2, R611.1, U610.4 (IN-)
/Isolated trigger input and photodiode front end/PHOTO_THRESH: C614.1, R617.2, U611.4 (IN-)
/Isolated trigger input and photodiode front end/TRIG_ISO_IN: J600.1 (SIG), R600.1
/Isolated trigger input and photodiode front end/TRIG_ISO_RTN: D600.2 (A), J600.2 (SHELL), J600.3 (SHELL), J600.4 (SHELL), U600.3 (K)
/Isolated trigger input and photodiode front end/TRIG_LED_A: D600.1 (K), R600.2, U600.1 (A)
/Isolated trigger input and photodiode front end/TRIG_OPTO_OUT: R601.1, U600.5 (VO)
GND: C600.2, C611.2, C612.2, C613.2, C614.2, C615.2, D601.3 (GND), J601.2, R613.2, U600.4 (GND), U610.2 (V-), U611.2 (VEE), U612.2 (VSS), U612.6 (A0); also elsewhere on the board
PHOTO_EDGE: R616.2; also elsewhere on the board
PHOTO_MONITOR: C610.2, R611.2, R614.1, U610.1 (OUT); also elsewhere on the board
POWER_SCL: U612.5 (SCL); also elsewhere on the board
POWER_SDA: U612.4 (SDA); also elsewhere on the board
TRIGGER_ISO: R601.2; also elsewhere on the board

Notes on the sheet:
EVENT INPUTS - EDGES TIMESTAMPED BY THE MCU TIMER (GPIOTE + PPI), SAME PATH AS ADC DRDY
Isolated trigger input
3.0-5.0 V logic lights the TLP2761 LED through 620R; D600 clamps reverse polarity. Output to TRIGGER_ISO for timer capture.
Photodiode transimpedance amplifier
Passive photodiode into TLV9061, 33k || 15 pF feedback; output also to SAADC (PHOTO_MONITOR) for threshold calibration.
Edge comparator
TLV7011 with 1M hysteresis feedback drives PHOTO_EDGE for timer capture.
Threshold DAC
MCP4725 on the power I2C bus (0x60) sets the comparator threshold through a 1k/100 nF filter.
Sheet notes
ISOLATION BARRIER: J600, R600, D600 and U600 pins 1-3 are the isolated side. Keep >= 8 mm creepage and clearance to all other copper (slot under U600). J600 shell is not board GND.
Trigger input 3.0-5.0 V logic, active high, 2-6 mA LED current. U600 inverts: trigger high gives TRIGGER_ISO low; firmware captures both edges.
Photodiode: passive sensor only (e.g. BPW34). Not isolated: treat as participant-side like the electrodes. TIA Vout = 50 mV + Iph x 33k; DAC POR code 0 = no edges until calibrated.

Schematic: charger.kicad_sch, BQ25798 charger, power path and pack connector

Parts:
C400: 10u 25V X7R 1206 (VBUS); C_1206_3216Metric; MPN GRM31CR71E106KA12L
C401: 10u 25V X7R 1206 (VBUS, behind OVP soft start); C_1206_3216Metric; MPN GRM31CR71E106KA12L
C402: 100n 50V X7R (VBUS, at pin); C_0603_1608Metric; MPN GCM188R71H104KA57D
C403, C404, C405: 10u 25V X7R 1206 (PMID); C_1206_3216Metric; MPN GRM31CR71E106KA12L
C406: 100n 50V X7R (PMID, at pin); C_0603_1608Metric; MPN GCM188R71H104KA57D
C407: 47n 25V X7R (BTST1); C_0603_1608Metric; MPN GCM188R71H473KA55D
C408: 47n 25V X7R (BTST2); C_0603_1608Metric; MPN GCM188R71H473KA55D
C409: 4.7u 10V X7R (REGN); C_0805_2012Metric; MPN GRM21BR71C475KE51L
C410, C411, C412, C413, C414: 22u 25V X7R 1210 (SYS); C_1210_3225Metric; MPN GRM32ER71E226KE15L
C415: 100n 50V X7R (SYS, at pin); C_0603_1608Metric; MPN GCM188R71H104KA57D
C416: 100u 16V OS-CON polymer (SYS hold-up); CP_Elec_10x7.9; MPN 16SVP100M
C417, C418: 10u 25V X7R 1206 (BAT); C_1206_3216Metric; MPN GRM31CR71E106KA12L
D401: CHARGE LED green (LTST-C190GKT); LED_0603_1608Metric; MPN LTST-C190GKT
D402: BAT54 (button sense, blocks QON back-feed); SOT-23; MPN BAT54,215
J401: PACK: + / - / NTC 103AT (JST PH, keyed); JST_PH_S3B-PH-K_1x03_P2.00mm_Horizontal; MPN S3B-PH-K-S
L400: 1.0uH XFL4020-102ME (Isat >= 3 A); L_Coilcraft_XxL4020; MPN XFL4020-102MEC
Q400: CSD17571Q2 (ship FET); Texas_DQK_SON-6_2x2mm_CSD17571Q2; MPN CSD17571Q2
Q401: BSS138 (CE pull-down); SOT-23; MPN BSS138
R400: 100R 1% (BATP sense); R_0603_1608Metric; MPN ERJ-3EKF1000V
R401: 6.04k 1% (PROG: 2S, 1.5 MHz); R_0603_1608Metric; MPN ERJ-3EKF6041V
R402: 27.0k 1%; R_0603_1608Metric; MPN ERJ-3EKF2702V
R403: 10.0k 1%; R_0603_1608Metric; MPN ERJ-3EKF1002V
R404: 5.23k 1%; R_0603_1608Metric; MPN ERJ-3EKF5231V
R405: 30.1k 1%; R_0603_1608Metric; MPN ERJ-3EKF3012V
R406: 100k; R_0603_1608Metric; MPN ERJ-3EKF1003V
R407: 2.2k; R_0603_1608Metric; MPN ERJ-3EKF2201V
R408: 10k; R_0603_1608Metric; MPN ERJ-3EKF1002V
SW400: POWER (hold 1 s: on; 10 s: system reset); SW_SPST_TL3342; MPN TL3342F160QG
U400: BQ25798RQMR (I2C 0x6B); Texas_RQM0029A_VQFN-HR-29_4x4mm; MPN BQ25798RQMR

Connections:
+3V3: R408.1; also elsewhere on the board
/BQ25798 charger, power path and pack connector/CHG_BATP: R400.2, U400.18 (BATP)
/BQ25798 charger, power path and pack connector/CHG_BTST1: C407.1, U400.4 (BTST1)
/BQ25798 charger, power path and pack connector/CHG_BTST2: C408.1, U400.19 (BTST2)
/BQ25798 charger, power path and pack connector/CHG_CE_N: Q401.3 (D), R406.2, U400.13 (~CE)
/BQ25798 charger, power path and pack connector/CHG_ILIM: R402.2, R403.1, U400.17 (ILIM_HIZ)
/BQ25798 charger, power path and pack connector/CHG_LED_A: D401.2 (A), R407.2
/BQ25798 charger, power path and pack connector/CHG_PMID: C403.1, C404.1, C405.1, C406.1, U400.29 (PMID)
/BQ25798 charger, power path and pack connector/CHG_PROG: R401.1, U400.20 (PROG)
/BQ25798 charger, power path and pack connector/CHG_QON_N: D402.3 (K), SW400.1, U400.12 (~QON)
/BQ25798 charger, power path and pack connector/CHG_SDRV: Q400.3 (G), U400.24 (SDRV)
/BQ25798 charger, power path and pack connector/CHG_STAT_N: D401.1 (K), U400.1 (~STAT)
/BQ25798 charger, power path and pack connector/CHG_SW1: C407.2, L400.1, U400.28 (SW1)
/BQ25798 charger, power path and pack connector/CHG_SW2: C408.2, L400.2, U400.26 (SW2)
/BQ25798 charger, power path and pack connector/CHG_TS: J401.3, R404.2, R405.1, U400.16 (TS)
/BQ25798 charger, power path and pack connector/PACK_IN: J401.1, Q400.1 (D), Q400.2 (D), Q400.5 (D), Q400.6 (D), R400.1
/BQ25798 charger, power path and pack connector/REGN: C409.1, R402.1, R404.1, R406.1, R407.1, U400.5 (REGN)
CHARGER_INT_N: U400.21 (~INT); also elsewhere on the board
CHARGE_REQUEST: Q401.1 (G); also elsewhere on the board
GND: C400.2, C401.2, C402.2, C403.2, C404.2, C405.2, C406.2, C409.2, C410.2, C411.2, C412.2, C413.2, C414.2, C415.2, C416.2, C417.2, C418.2, J401.2, Q401.2 (S), R401.2, R403.2, R405.2, SW400.2, U400.10 (ACDRV2), U400.11 (ACDRV1), U400.27 (GND); also elsewhere on the board
PACK_POS: C417.1, C418.1, Q400.4 (S), U400.22 (BAT), U400.23 (BAT); also elsewhere on the board
POWER_BUTTON_N: D402.1 (A), R408.2; also elsewhere on the board
POWER_SCL: U400.14 (SCL); also elsewhere on the board
POWER_SDA: U400.15 (SDA); also elsewhere on the board
SYS: C410.1, C411.1, C412.1, C413.1, C414.1, C415.1, C416.1, U400.25 (SYS); also elsewhere on the board
USB_5V: C400.1, C401.1, C402.1, U400.2 (VBUS), U400.3 (VBUS), U400.8 (VAC2), U400.9 (VAC1); also elsewhere on the board

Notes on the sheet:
BQ25798 2S CHARGER, POWER PATH, SHIP FET AND PACK CONNECTOR - CHARGE ONLY WITH ELECTRODES DISCONNECTED
BQ25798 buck-boost charger
Single input on VBUS: VAC1/VAC2 tied to VBUS and ACDRV1/2 to GND (no input FETs).
D+/D- unconnected: USB data stays with the MCU.
Input and PMID capacitors
VBUS: 2 x 10 uF + 100 nF as TI recommends (Step 14: the OVP soft start, not the connector, charges this bulk). PMID: 3 x 10 uF + 100 nF. 100 nF parts
at the pins.
Converter: inductor and bootstrap
1.0 uH for the 1.5 MHz setting (TI: 1.5 MHz requires 1 uH). Isat must exceed the input or charge current plus half
ripple.
SYS capacitance and hold-up
5 x 22 uF X7R + 100 uF OS-CON + 100 nF. Step 10 needs >= 24 uF effective at average load (aim 127 uF) so SYS_OK resets the ADC before AVDD leaves regulation.
Battery side and ship FET
Q400 between pack and BAT, source on the charger side: its body diode blocks pack discharge in ship mode. BATP senses the pack side through 100R.
Configuration straps
PROG 6.04k: 2S, 1.5 MHz. ILIM_HIZ = REGN x 10/37: hardware input ceiling about 0.37 A (max 0.44 A), below the 500 mA USB default. TS: 5.23k/30.1k window for a 103AT NTC
(charge 0-60 C, JEITA).
Charge enable
CE low enables charging. R406 holds CE high from REGN; Q401 pulls it low only while CHARGE_REQUEST is high, so charging stays
off whenever the MCU is not running.
Charge LED, power button
STAT LED lit from REGN (USB present): on while charging, 1 Hz blink on fault. POWER drives QON; BAT54 gives the MCU a 3.3 V-safe copy
(QON idles near 3.2 V).
Sheet notes
On battery the BQ25798 does not switch: its battery FET connects the pack to SYS. With USB present it powers SYS and charges the pack; SERVICE_OK keeps the ADC off.
Firmware: read TUSB320 advertised current, then set EN_EXTILIM = 0 and IINDPM to the allowed budget; disable AUTO_INDET_EN (D+/D- not connected); set ICHG 0.5 A, VREG 8.4 V, JEITA limits from the pack
data sheet; service or disable the 40 s watchdog (on expiry the hardware ceiling returns).
Soft-off: firmware writes SDRV_CTRL = 10 (ship mode); Q400 opens and the whole board, supervisor dividers included, loses power. Hold POWER 1 s or plug USB to wake. Holding POWER 10 s forces a system
power reset.
Layout: follow the TI layout guide - VBUS/PMID/SYS/BAT capacitors and the 100 nF parts at the pins, short SW1/SW2 loop, BATP Kelvin to the pack side of Q400. Keep the converter away from the electrode
inputs.
